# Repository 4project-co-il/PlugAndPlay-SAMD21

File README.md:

# PlugAndPlay: SAMD21 Dev Board
This is the repository with the files for PlugAndPlay SAMD21 Development Board.

The PlugAndPlay system is an arduino-based environment that allows easier connections between the parts
and intended to create a more "product-like" projects with permanent connections, compared to a breadboard.

PlugAndPlay parts do not require any soldering to connect. Just plug the cable to the connectors and you are ready to go.
In the worst case, you might need to tighten few screws on a terminal block.

Most of the parts in the PlugAndPlay system communicate via I2C protocol. 
The connectors between the parts have 6 lines: 2 lines to provide the power (3.3V VCC and GND), 2 lines for the I2C communication and additional 2 lines for the interrupts, that can be used as digital inputs or outputs in some cases.
The interrupts are handled by the Event Based Framework ([EBF](https://github.com/4project-co-il/EBF)) in the background. No polling is needed in the software.
A button pressed? Event function will be called in your code to handle that change.

Using the interrupts allows creation of very low-power projects, as well as controllers with fast responding to changes.
The PlugAndPlay SAMD21 Dev Board consumes only 21.5 uA in deep sleep. Yes, 21.5 micro-amper!
The system is designed to work with 3.3V power supply, but can go down to about 2V as well, so even less power consumption is possible for very low power needs.

No need to worry about the correct wires connection, accidental inversion of I2C lines, or even worse, the VCC and GND.
No need to worry about the I2C addresses as well. Pull-up resistors if you connect few parts in serial, are those needed or not?
What port should I connect the part? Is is PWM complatible? No more wories like that.
Just plug the connectors and start playing with the code. As easy as that.

Every PlugAndPlay device contains an EEPROM with its identification, that allows the PnP code to match between the code instance implementing a logic to the physical device connected to one of the PnP ports on the SAMD21 Dev Board.

Communication is not the only thing handled by the PnP system. Power distribution is easily managed as well.
Need to have a 12V relay, 5V servo and 3.3V for the logic? No problem at all...
Plug the power cables between the parts, add needed regulator to the board and you're done.

The board is manufactured by the [4project.co.il](https://www.4project.co.il/).\
You will need the Event Based Framework ([EBF](https://github.com/4project-co-il/EBF)) to program the board.

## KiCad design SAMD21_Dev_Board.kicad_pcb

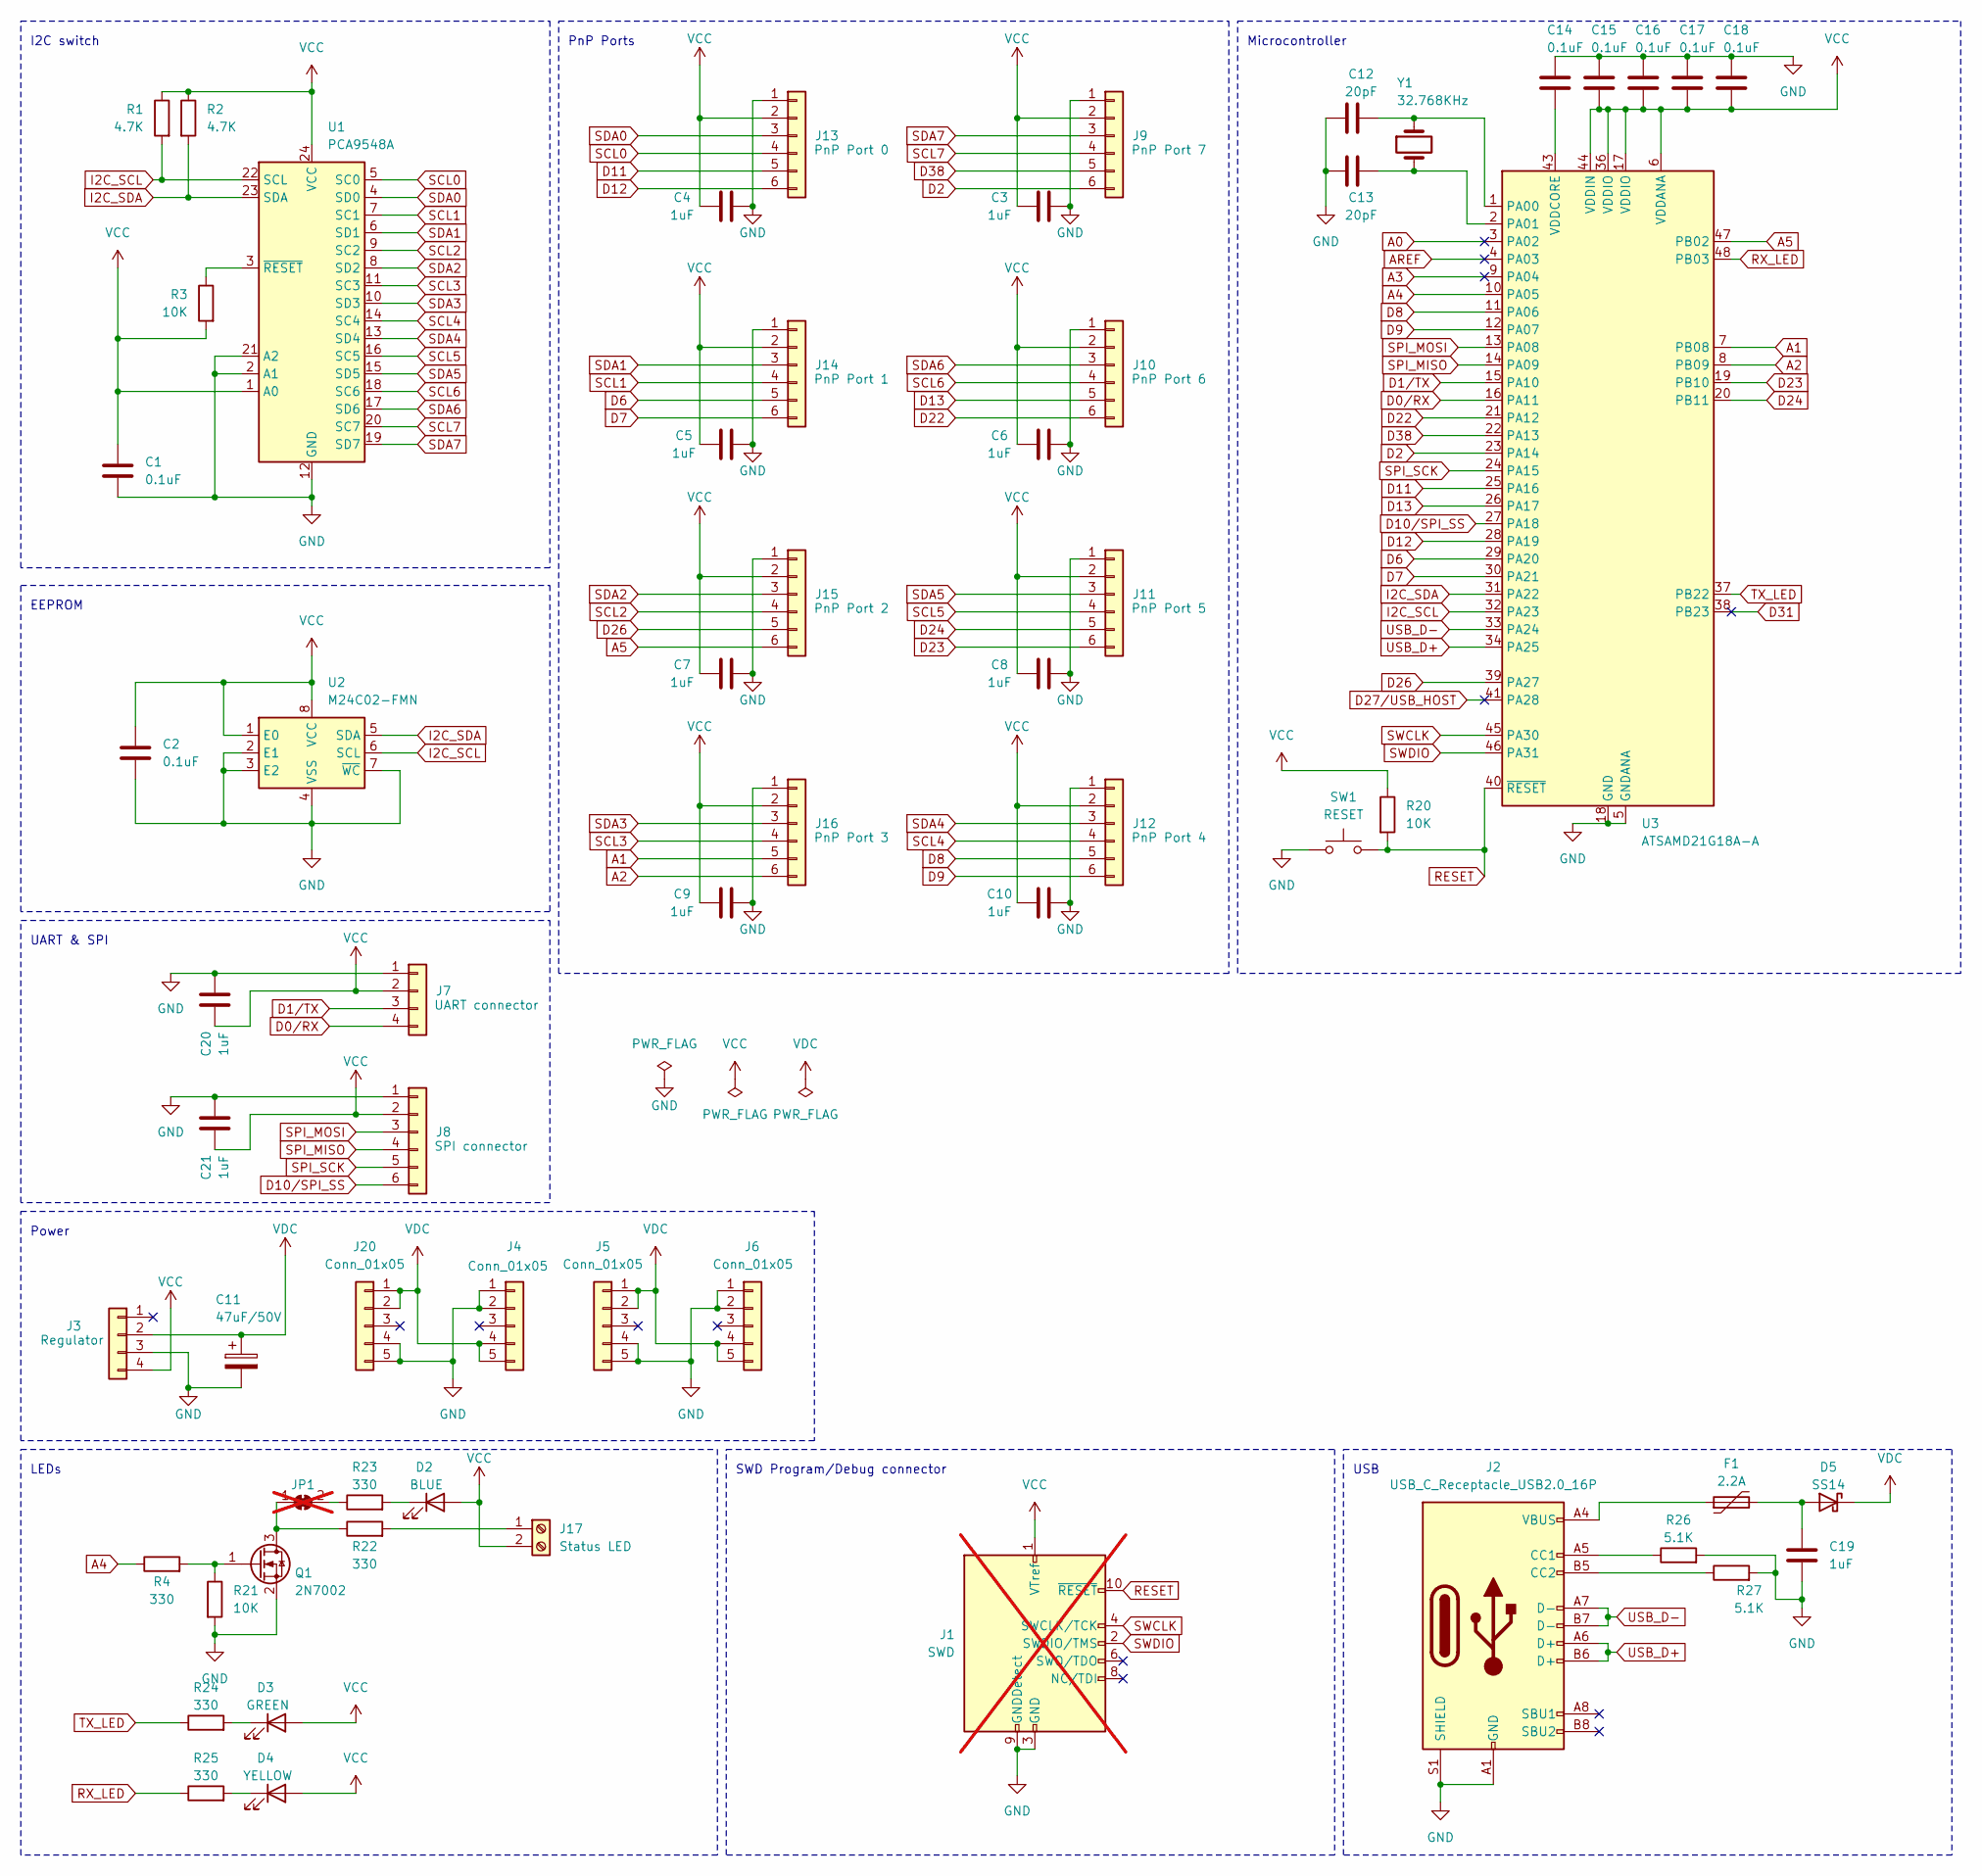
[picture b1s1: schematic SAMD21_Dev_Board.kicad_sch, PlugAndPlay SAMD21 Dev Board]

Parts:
C1, C2, C14, C15, C16, C17, C18: 0.1uF; C_0603_1608Metric; MPN C14663
C3, C4, C5, C6, C7, C8, C9, C10, C19, C20, C21: 1uF; C_0603_1608Metric; MPN C1592
C11: 47uF/50V; C_Elec_6.3x7.7; MPN C3349
C12, C13: 20pF; C_0603_1608Metric; MPN C105621
D2: BLUE; LED_0603_1608Metric; MPN C965807
D3: GREEN; LED_0603_1608Metric; MPN C965804
D4: YELLOW; LED_0603_1608Metric; MPN C965802
D5: SS14; D_SMA; MPN C2480
F1: 2.2A; Fuse_1206_3216Metric; MPN C89654
J1: SWD; PinHeader_2x05_P1.27mm_Vertical; not fitted
J2: USB_C_Receptacle_USB2.0_16P; USB_C_Receptacle_G-Switch_GT-USB-7010ASV; MPN C2988369
J3: PinSocket_1x04_P2.54mm_Vertical_SMD_Pin1Left; MPN C20071191
J4, J6: Conn_01x05; PinSocket_1x05_P2.54mm_Vertical_SMD_Pin1Left; MPN RealRun
J5, J20: Conn_01x05; PinSocket_1x05_P2.54mm_Vertical_SMD_Pin1Right; MPN RealRun
J7: JST_SH_SM04B-SRSS-TB_1x04-1MP_P1.00mm_Horizontal; MPN C7430446
J8, J9, J10, J11, J12, J13, J14, J15, J16: JST_SH_SM06B-SRSS-TB_1x06-1MP_P1.00mm_Horizontal; MPN C7430448
J17: Status LED; TerminalBlock_TE_282834-2_1x02_P2.54mm_Horizontal; MPN C695629
JP1: SolderJumper_2_Bridged; SolderJumper-2_P1.3mm_Bridged_RoundedPad1.0x1.5mm; not fitted
Q1: 2N7002; SOT-23; MPN C916396
R1, R2: 4.7K; R_0603_1608Metric; MPN C23162
R3, R20, R21: 10K; R_0603_1608Metric; MPN C25804
R4, R22, R23, R24, R25: 330; R_0603_1608Metric; MPN C23138
R26, R27: 5.1K; R_0603_1608Metric; MPN C23186
SW1: RESET; SW_Push_1P1T_XKB_TS-1187A; MPN C318884
U1: PCA9548A; TSSOP-24_4.4x7.8mm_P0.65mm; MPN C295762
U2: M24C02-FMN; SOIC-8_3.9x4.9mm_P1.27mm; MPN C114502
U3: ATSAMD21G18A-A; TQFP-48_7x7mm_P0.5mm; MPN C78624
Y1: 32.768KHz; Crystal_SMD_3215-2Pin_3.2x1.5mm; MPN C620155

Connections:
A0: U3.3 (PA02)
A1: J16.5, U3.7 (PB08)
A2: J16.6, U3.8 (PB09)
A3: U3.9 (PA04)
A4: R4.1, U3.10 (PA05)
A5: J15.6, U3.47 (PB02)
AREF: U3.4 (PA03)
D0/RX: J7.4, U3.16 (PA11)
D1/TX: J7.3, U3.15 (PA10)
D2: J9.6, U3.23 (PA14)
D6: J14.5, U3.29 (PA20)
D7: J14.6, U3.30 (PA21)
D8: J12.5, U3.11 (PA06)
D9: J12.6, U3.12 (PA07)
D10/SPI_SS: J8.6, U3.27 (PA18)
D11: J13.5, U3.25 (PA16)
D12: J13.6, U3.28 (PA19)
D13: J10.5, U3.26 (PA17)
D22: J10.6, U3.21 (PA12)
D23: J11.6, U3.19 (PB10)
D24: J11.5, U3.20 (PB11)
D26: J15.5, U3.39 (PA27)
D27/USB_HOST: U3.41 (PA28)
D31: U3.38 (PB23)
D38: J9.5, U3.22 (PA13)
GND: C1.2, C2.2, C3.1, C4.1, C5.2, C6.1, C7.1, C8.1, C9.1, C10.1, C11.2, C12.1, C13.1, C14.1, C15.1, C16.1, C17.1, C18.1, C19.2, C20.1, C21.1, J1.3 (GND), J1.5 (GND), J1.9 (GNDDetect), J2.A1 (GND), J2.A12 (GND), J2.B1 (GND), J2.B12 (GND), J2.S1 (SHIELD), J3.3, J4.1, J4.2, J5.4, J5.5, J6.1, J6.2, J7.1, J8.1, J9.1, J10.1, J11.1, J12.1, J13.1, J14.1, J15.1, J16.1, J20.4, J20.5, Q1.2 (S), R21.2, R26.2, R27.2, SW1.1, U1.2 (A1), U1.12 (GND), U1.21 (A2), U2.2 (E1), U2.3 (E2), U2.4 (VSS), U2.7 (~WC), U3.5 (GNDANA), U3.18 (GND), U3.35 (GND), U3.42 (GND)
I2C_SCL: R1.2, U1.22 (SCL), U2.6 (SCL), U3.32 (PA23)
I2C_SDA: R2.2, U1.23 (SDA), U2.5 (SDA), U3.31 (PA22)
unnamed: D2.1 (K), R23.2
unnamed: D3.1 (K), R24.2
unnamed: D4.1 (K), R25.2
unnamed: C19.1, D5.2 (A), F1.2
unnamed: F1.1, J2.A4 (VBUS), J2.A9 (VBUS), J2.B4 (VBUS), J2.B9 (VBUS)
unnamed: J2.A5 (CC1), R26.1
unnamed: J2.B5 (CC2), R27.1
unnamed: J17.1, R22.2
unnamed: JP1.1 (A), Q1.3 (D), R22.1
unnamed: JP1.2 (B), R23.1
unnamed: Q1.1 (G), R4.2, R21.1
unnamed: R3.1, U1.3 (~RESET)
unnamed: C12.2, U3.1 (PA00), Y1.1
unnamed: C13.2, U3.2 (PA01), Y1.2
unnamed: C14.2, U3.43 (VDDCORE)
RESET: J1.10 (~RESET), R20.2, SW1.2, U3.40 (~RESET)
RX_LED: R25.1, U3.48 (PB03)
SCL0: J13.4, U1.5 (SC0)
SCL1: J14.4, U1.7 (SC1)
SCL2: J15.4, U1.9 (SC2)
SCL3: J16.4, U1.11 (SC3)
SCL4: J12.4, U1.14 (SC4)
SCL5: J11.4, U1.16 (SC5)
SCL6: J10.4, U1.18 (SC6)
SCL7: J9.4, U1.20 (SC7)
SDA0: J13.3, U1.4 (SD0)
SDA1: J14.3, U1.6 (SD1)
SDA2: J15.3, U1.8 (SD2)
SDA3: J16.3, U1.10 (SD3)
SDA4: J12.3, U1.13 (SD4)
SDA5: J11.3, U1.15 (SD5)
SDA6: J10.3, U1.17 (SD6)
SDA7: J9.3, U1.19 (SD7)
SPI_MISO: J8.4, U3.14 (PA09)
SPI_MOSI: J8.3, U3.13 (PA08)
SPI_SCK: J8.5, U3.24 (PA15)
SWCLK: J1.4 (SWCLK/TCK), U3.45 (PA30)
SWDIO: J1.2 (SWDIO/TMS), U3.46 (PA31)
TX_LED: R24.1, U3.37 (PB22)
USB_D+: J2.A6 (D+), J2.B6 (D+), U3.34 (PA25)
USB_D-: J2.A7 (D-), J2.B7 (D-), U3.33 (PA24)
VCC: C1.1, C2.1, C3.2, C4.2, C5.1, C6.2, C7.2, C8.2, C9.2, C10.2, C15.2, C16.2, C17.2, C18.2, C20.2, C21.2, D2.2 (A), D3.2 (A), D4.2 (A), J1.1 (VTref), J3.4, J7.2, J8.2, J9.2, J10.2, J11.2, J12.2, J13.2, J14.2, J15.2, J16.2, J17.2, R1.1, R2.1, R3.2, R20.1, U1.1 (A0), U1.24 (VCC), U2.1 (E0), U2.8 (VCC), U3.6 (VDDANA), U3.17 (VDDIO), U3.36 (VDDIO), U3.44 (VDDIN)
VDC: C11.1, D5.1 (K), J3.2, J4.4, J4.5, J5.1, J5.2, J6.4, J6.5, J20.1, J20.2

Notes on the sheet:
Microcontroller
USB
Power
PnP Ports
LEDs
UART & SPI
I2C switch
SWD Program/Debug connector
EEPROM

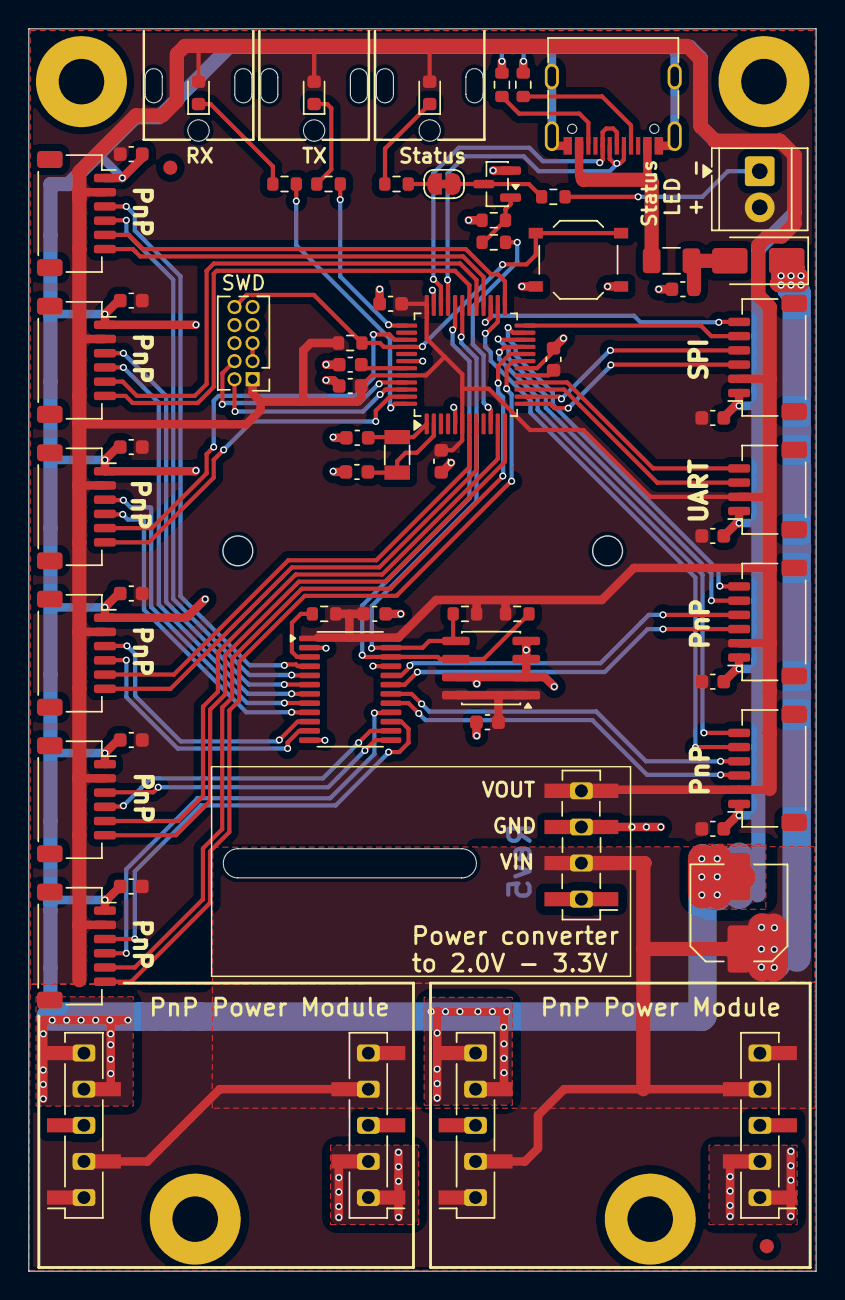
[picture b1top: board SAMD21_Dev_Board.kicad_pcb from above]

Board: 2 copper layers, 55.3 x 87.3 mm, 63 parts (0 on the bottom side), 66 nets.

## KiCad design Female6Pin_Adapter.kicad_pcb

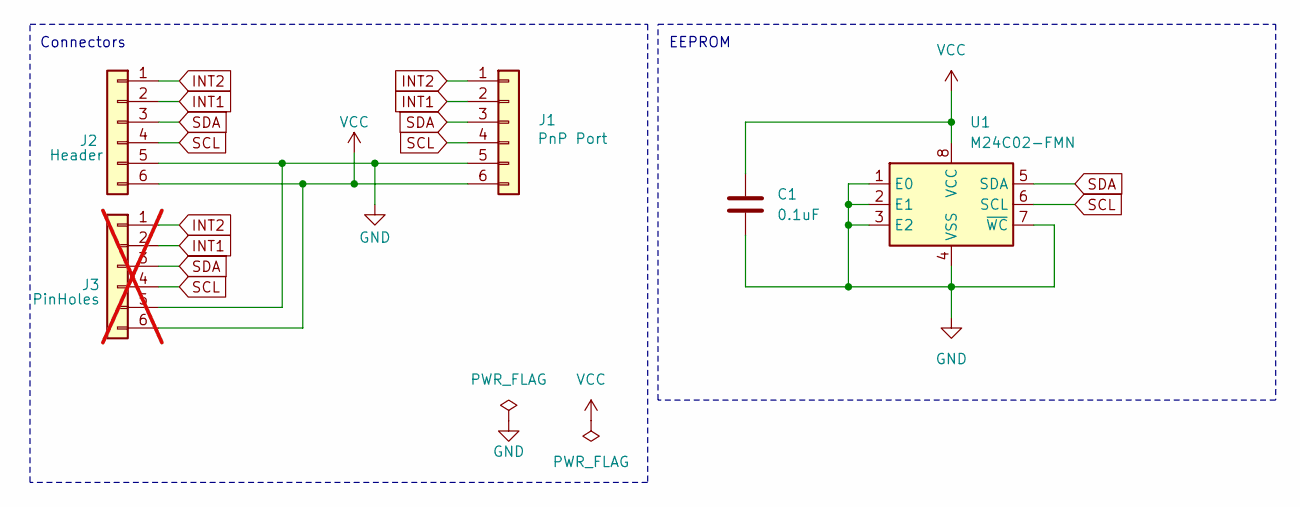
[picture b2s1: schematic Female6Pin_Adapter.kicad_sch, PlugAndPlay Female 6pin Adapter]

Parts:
C1: 0.1uF; C_0603_1608Metric; MPN C14663
J1: JST_SH_SM06B-SRSS-TB_1x06-1MP_P1.00mm_Horizontal; MPN C7430448
J2: PinHeader_1x06_P2.54mm_Horizontal_SMD; MPN C5142239
J3: Conn_01x06; PinHeader_1x06_P2.54mm_Vertical; not fitted
U1: M24C02-FMN; SOIC-8_3.9x4.9mm_P1.27mm; MPN C114502

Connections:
GND: C1.2, J1.5, J2.5, J3.5, U1.1 (E0), U1.2 (E1), U1.3 (E2), U1.4 (VSS), U1.7 (~WC)
INT1: J1.2, J2.2, J3.2
INT2: J1.1, J2.1, J3.1
SCL: J1.4, J2.4, J3.4, U1.6 (SCL)
SDA: J1.3, J2.3, J3.3, U1.5 (SDA)
VCC: C1.1, J1.6, J2.6, J3.6, U1.8 (VCC)

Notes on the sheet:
EEPROM
Connectors

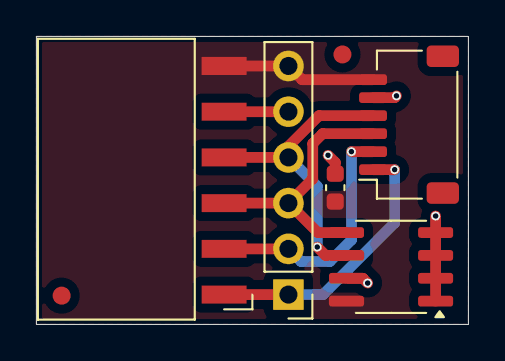
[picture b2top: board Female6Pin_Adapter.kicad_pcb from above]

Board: 2 copper layers, 24.0 x 16.0 mm, 5 parts (0 on the bottom side), 6 nets.

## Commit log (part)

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2025-01-19 Initial upload
2025-02-07 Update gitignore
2025-02-07 SWD port moved closer to the edge to be able use the pogo pins clip
2025-02-07 Added bootloader for PnP SAMD21
2025-02-09 Minor cosmetic trace routing changes
2025-02-12 Fiducials change to 1mm footprint Using D4 line for status LED (can do PWM) instead of D13 Bootloader updated accordingly
2025-03-10 Power modules are set wider, to have more space for XT30 connectors. Interrupt lines were changed based on the SAMD21 interrupt mapping. PnP connector lines were swapped to match colors on the JST-SH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
2025-03-10 Kikit panelization
2025-03-11 Make .gitignore more generic
2025-03-11 Make gitignore more generic
2025-03-30 Adding missing holes on the bottom side. Adding holes in the middle of the board for potential add-ons.
2025-03-30 Bootloader update based on Rev2 design
2025-04-29 Added thermal relief
2025-05-11 Adding colors to GND,VCC and VDC nets. VIAs review.
2025-05-11 Reset line adjustment
2025-05-11 Update DRC rules configuration
2025-05-18 Back to cables with GND pin1, VCC pin2
2025-05-19 Panel framing on all 4 sides
2025-07-18 Moved the power modules location to have 1mm more spacing between them
2025-07-20 Adding Rev number to the back copper layer
2025-07-24 Ground plane return paths improvements
2025-08-31 Increase solder paste opennings by 5% for elect.capacitor and headers. Decrease screw terminal holes from 1.1mm to 1.0mm.
2026-01-11 Chanigng I2C mux and EEPROM I2C addresses to 0x01
